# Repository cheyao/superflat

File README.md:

# Superflat - a ultra low profile bluetooth keyboard

A super flat PG1316 bluetooth split keyboard - The thickness is projected to be within 1cm. And the dimensions will be around  12x12cm

The design has it's custom USB port, battery protection & charging circuit and bluetooth nRF52840 integration.

The firmware that will be used will be zmk, and the projected battery life will be 2 months

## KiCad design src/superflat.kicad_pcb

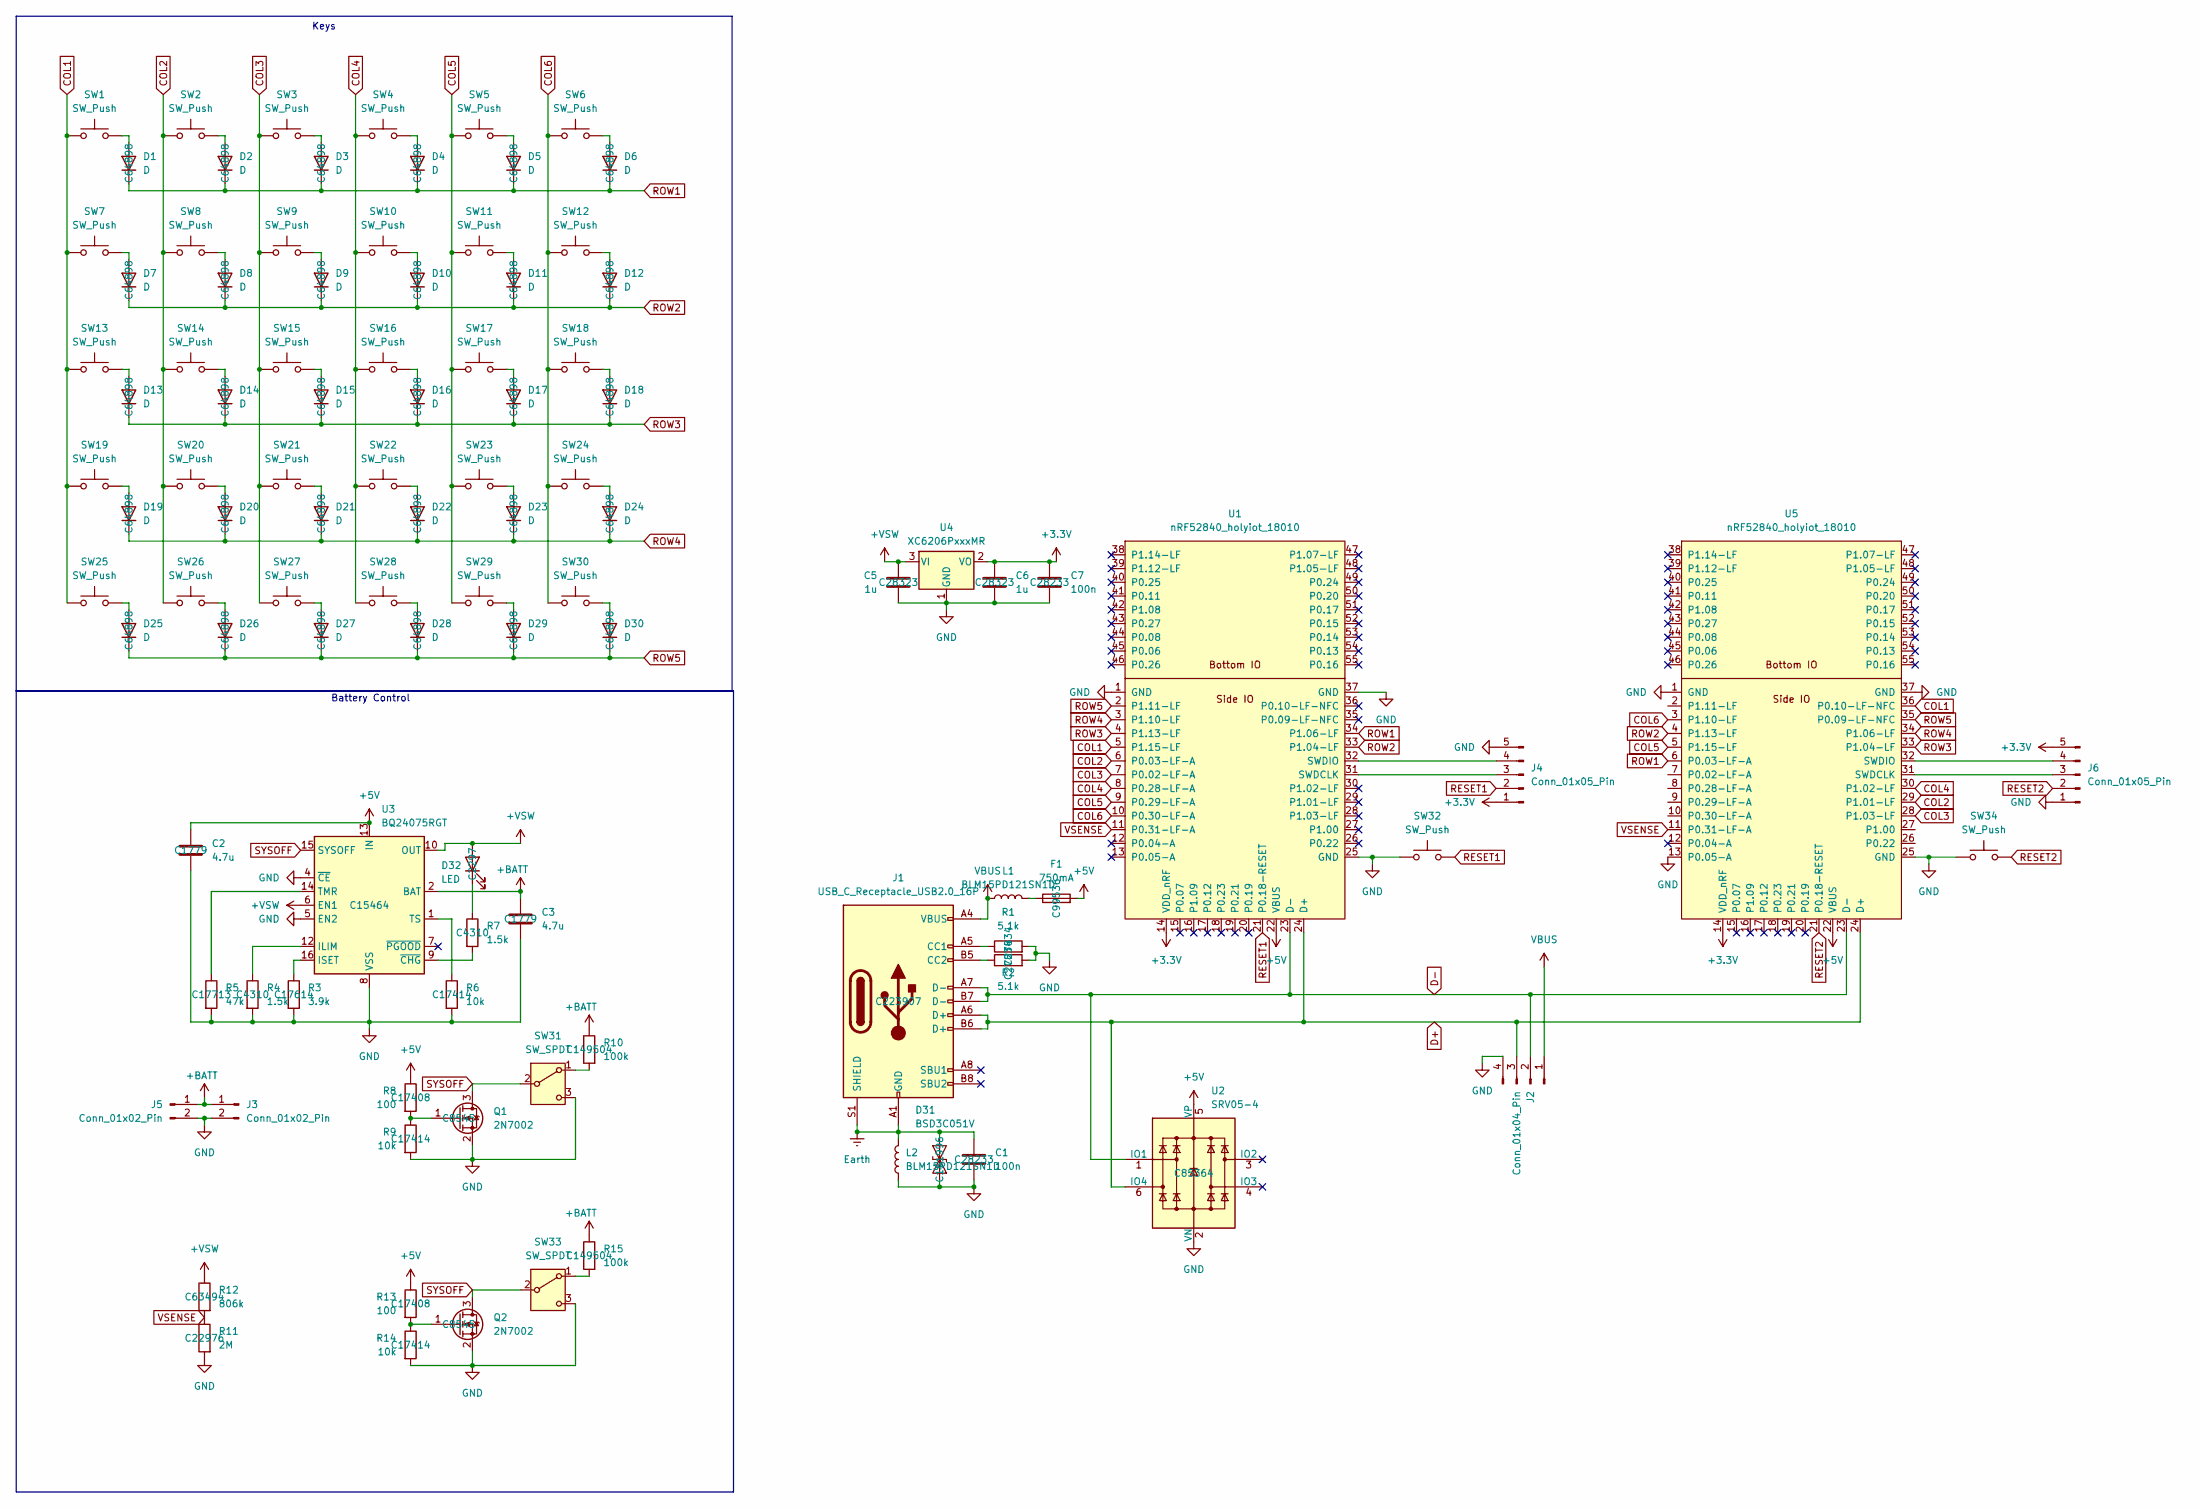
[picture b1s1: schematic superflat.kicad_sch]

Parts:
C1, C7: 100n; C_0805_2012Metric_Pad1.18x1.45mm_HandSolder; LCSC C28233
C2, C3: 4.7u; C_0805_2012Metric_Pad1.18x1.45mm_HandSolder; LCSC C1779
C5, C6: 1u; C_0805_2012Metric_Pad1.18x1.45mm_HandSolder; LCSC C28323
D1, D2, D3, D4, D5, D6, D7, D8, D9, D10, D11, D12, D13, D14, D15, D16, D17, D18, D19, D20, D21, D22, D23, D24, D25, D26, D27, D28, D29, D30: D; D_SOD-123F; LCSC C64898
D31: BSD3C051V; D_SMA; LCSC C151996
D32: LED; LED_0805_2012Metric_Pad1.15x1.40mm_HandSolder; LCSC C2297
F1: 750mA; Fuse_1206_3216Metric_Pad1.42x1.75mm_HandSolder; LCSC C99536
J1: USB_C_Receptacle_USB2.0_16P; USB_C_Receptacle_HRO_TYPE-C-31-M-14; LCSC C223907
J2: Conn_01x04_Pin; PinHeader_1x04_P2.54mm_Vertical
J3, J5: Conn_01x02_Pin; PinHeader_1x02_P2.54mm_Vertical
J4, J6: Conn_01x05_Pin; PinHeader_1x05_P2.54mm_Vertical
L1, L2: BLM15PD121SN1D; L_0402_1005Metric_Pad0.77x0.64mm_HandSolder
Q1, Q2: 2N7002; SOT-23; LCSC C8545
R1, R2: 5.1k; R_0805_2012Metric_Pad1.20x1.40mm_HandSolder; LCSC C27834
R3: 3.9k; R_0805_2012Metric_Pad1.20x1.40mm_HandSolder; LCSC C17614
R4, R7: 1.5k; R_0805_2012Metric_Pad1.20x1.40mm_HandSolder; LCSC C4310
R5: 47k; R_0805_2012Metric_Pad1.20x1.40mm_HandSolder; LCSC C17713
R6, R9, R14: 10k; R_0805_2012Metric_Pad1.20x1.40mm_HandSolder; LCSC C17414
R8, R13: 100; R_0805_2012Metric_Pad1.20x1.40mm_HandSolder; LCSC C17408
R10, R15: 100k; R_0805_2012Metric_Pad1.20x1.40mm_HandSolder; LCSC C149504
R11: 2M; R_0603_1608Metric_Pad0.98x0.95mm_HandSolder; LCSC C22976
R12: 806k; R_0805_2012Metric_Pad1.20x1.40mm_HandSolder; LCSC C63494
SW1, SW2, SW3, SW4, SW5, SW6, SW7, SW8, SW9, SW10, SW11, SW12, SW13, SW14, SW15, SW16, SW17, SW18, SW19, SW20, SW21, SW22, SW23, SW24, SW25, SW26, SW27, SW28, SW29, SW30: SW_Push; SW_PG1316S
SW31, SW33: SW_SPDT; Slide
SW32, SW34: SW_Push; SolderJumper-2_P1.3mm_Open_RoundedPad1.0x1.5mm
U1, U5: nRF52840_holyiot_18010; nRF52840_holyiot_18010_HS_simple
U2: SRV05-4; SOT-23-6-routable; LCSC C85364
U3: BQ24075RGT; VQFN-16-1EP_3x3mm_P0.5mm_EP1.6x1.6mm; LCSC C15464
U4: XC6206PxxxMR; SOT-23-3

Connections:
+3.3V: C6.1, C7.1, J4.1, J6.5, U1.14 (VDD_nRF), U4.2 (VO), U5.14 (VDD_nRF)
+5V: C2.1, F1.2, R8.1, R13.1, U1.22 (VBUS), U2.5 (VP), U3.13 (IN), U5.22 (VBUS)
+BATT: C3.1, J3.1, J5.1, R10.1, R15.1, U3.2 (BAT), U3.3 (BAT)
+VSW: C5.1, D32.2 (A), R12.1, U3.6 (EN1), U3.10 (OUT), U3.11 (OUT), U4.3 (VI)
COL1: SW1.1, SW7.1, SW13.1, SW19.1, SW25.1, U1.5 (P1.15-LF), U5.36 (P0.10-LF-NFC)
COL2: SW2.1, SW8.1, SW14.1, SW20.1, SW26.1, U1.6 (P0.03-LF-A), U5.29 (P1.01-LF)
COL3: SW3.1, SW9.1, SW15.1, SW21.1, SW27.1, U1.7 (P0.02-LF-A), U5.28 (P1.03-LF)
COL4: SW4.1, SW10.1, SW16.1, SW22.1, SW28.1, U1.8 (P0.28-LF-A), U5.30 (P1.02-LF)
COL5: SW5.1, SW11.1, SW17.1, SW23.1, SW29.1, U1.9 (P0.29-LF-A), U5.5 (P1.15-LF)
COL6: SW6.1, SW12.1, SW18.1, SW24.1, SW30.1, U1.10 (P0.30-LF-A), U5.3 (P1.10-LF)
D+: J1.A6 (D+), J1.B6 (D+), J2.3, SW4.MP, U1.24 (D+), U2.6 (IO4), U5.24 (D+)
D-: J1.A7 (D-), J1.B7 (D-), J2.2, U1.23 (D-), U2.1 (IO1), U5.23 (D-)
Earth: C1.1, D31.2 (A2), J1.A1 (GND), J1.A12 (GND), J1.B1 (GND), J1.B12 (GND), J1.S1 (SHIELD), L2.2
GND: C1.2, C2.2, C3.2, C5.2, C6.2, C7.2, D31.1 (A1), J2.4, J3.2, J4.5, J5.2, J6.1, L2.1, Q1.2 (S), Q2.2 (S), R1.2, R2.2, R3.2, R4.2, R5.2, R6.2, R9.2, R11.2, R14.2, SW5.MP, SW6.MP, SW7.MP, SW31.3 (C), SW32.1, SW33.3 (C), SW34.1, U1.1 (GND), U1.25 (GND), U1.37 (GND), U2.2 (VN), U3.4 (~CE), U3.5 (EN2), U3.8 (VSS), U3.17 (VSS), U4.1 (GND), U5.1 (GND), U5.13 (P0.05-A), U5.25 (GND), U5.37 (GND)
unnamed: D1.2 (A), SW1.2
unnamed: D2.2 (A), SW2.2
unnamed: D3.2 (A), SW3.2
unnamed: D4.2 (A), SW4.2
unnamed: D5.2 (A), SW5.2
unnamed: D6.2 (A), SW6.2
unnamed: D7.2 (A), SW7.2
unnamed: D8.2 (A), SW8.2
unnamed: D9.2 (A), SW9.2
unnamed: D10.2 (A), SW10.2
unnamed: D11.2 (A), SW11.2
unnamed: D12.2 (A), SW12.2
unnamed: D13.2 (A), SW13.2
unnamed: D14.2 (A), SW14.2
unnamed: D15.2 (A), SW15.2
unnamed: D16.2 (A), SW16.2
unnamed: D17.2 (A), SW17.2
unnamed: D18.2 (A), SW18.2
unnamed: D19.2 (A), SW19.2
unnamed: D20.2 (A), SW20.2
unnamed: D21.2 (A), SW21.2
unnamed: D22.2 (A), SW22.2
unnamed: D23.2 (A), SW23.2
unnamed: D24.2 (A), SW24.2
unnamed: D25.2 (A), SW25.2
unnamed: D26.2 (A), SW26.2
unnamed: D27.2 (A), SW27.2
unnamed: D28.2 (A), SW28.2
unnamed: D29.2 (A), SW29.2
unnamed: D30.2 (A), SW30.2
unnamed: D32.1 (K), R7.1
unnamed: F1.1, L1.2
unnamed: J1.A5 (CC1), R1.1
unnamed: J1.B5 (CC2), R2.1
unnamed: J4.3, U1.31 (SWDCLK)
unnamed: J4.4, U1.32 (SWDIO)
unnamed: J6.3, U5.31 (SWDCLK)
unnamed: J6.4, U5.32 (SWDIO)
unnamed: Q1.1 (G), R8.2, R9.1
unnamed: Q2.1 (G), R13.2, R14.1
unnamed: R10.2, SW31.1 (A)
unnamed: R15.2, SW33.1 (A)
unnamed: R4.1, U3.12 (ILIM)
unnamed: R3.1, U3.16 (ISET)
unnamed: R5.1, U3.14 (TMR)
unnamed: R6.1, U3.1 (TS)
unnamed: R7.2, U3.9 (~CHG)
RESET1: J4.2, SW32.2, U1.21 (P0.18-RESET)
RESET2: J6.2, SW34.2, U5.21 (P0.18-RESET)
ROW1: D1.1 (K), D2.1 (K), D3.1 (K), D4.1 (K), D5.1 (K), D6.1 (K), U1.34 (P1.06-LF), U5.6 (P0.03-LF-A)
ROW2: D7.1 (K), D8.1 (K), D9.1 (K), D10.1 (K), D11.1 (K), D12.1 (K), U1.33 (P1.04-LF), U5.4 (P1.13-LF)
ROW3: D13.1 (K), D14.1 (K), D15.1 (K), D16.1 (K), D17.1 (K), D18.1 (K), U1.4 (P1.13-LF), U5.33 (P1.04-LF)
ROW4: D19.1 (K), D20.1 (K), D21.1 (K), D22.1 (K), D23.1 (K), D24.1 (K), U1.3 (P1.10-LF), U5.34 (P1.06-LF)
ROW5: D25.1 (K), D26.1 (K), D27.1 (K), D28.1 (K), D29.1 (K), D30.1 (K), U1.2 (P1.11-LF), U5.35 (P0.09-LF-NFC)
SYSOFF: Q1.3 (D), Q2.3 (D), SW31.2 (B), SW33.2 (B), U3.15 (SYSOFF)
VBUS: J1.A4 (VBUS), J1.A9 (VBUS), J1.B4 (VBUS), J1.B9 (VBUS), J2.1, L1.1
VSENSE: R11.1, R12.2, U1.11 (P0.31-LF-A), U5.11 (P0.31-LF-A)

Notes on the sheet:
Battery Control
Keys

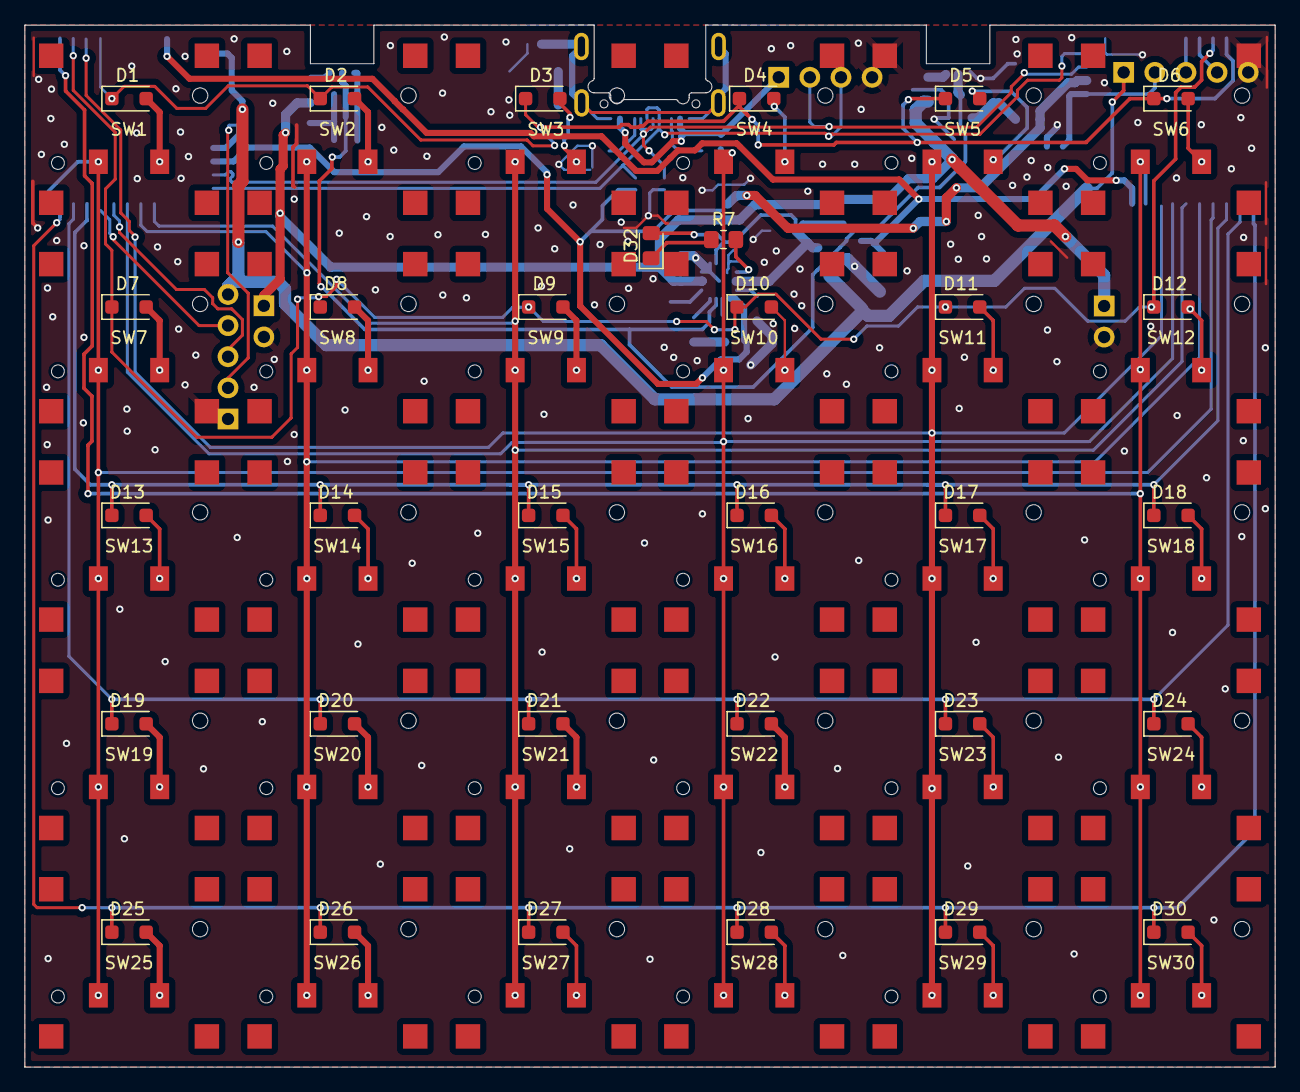
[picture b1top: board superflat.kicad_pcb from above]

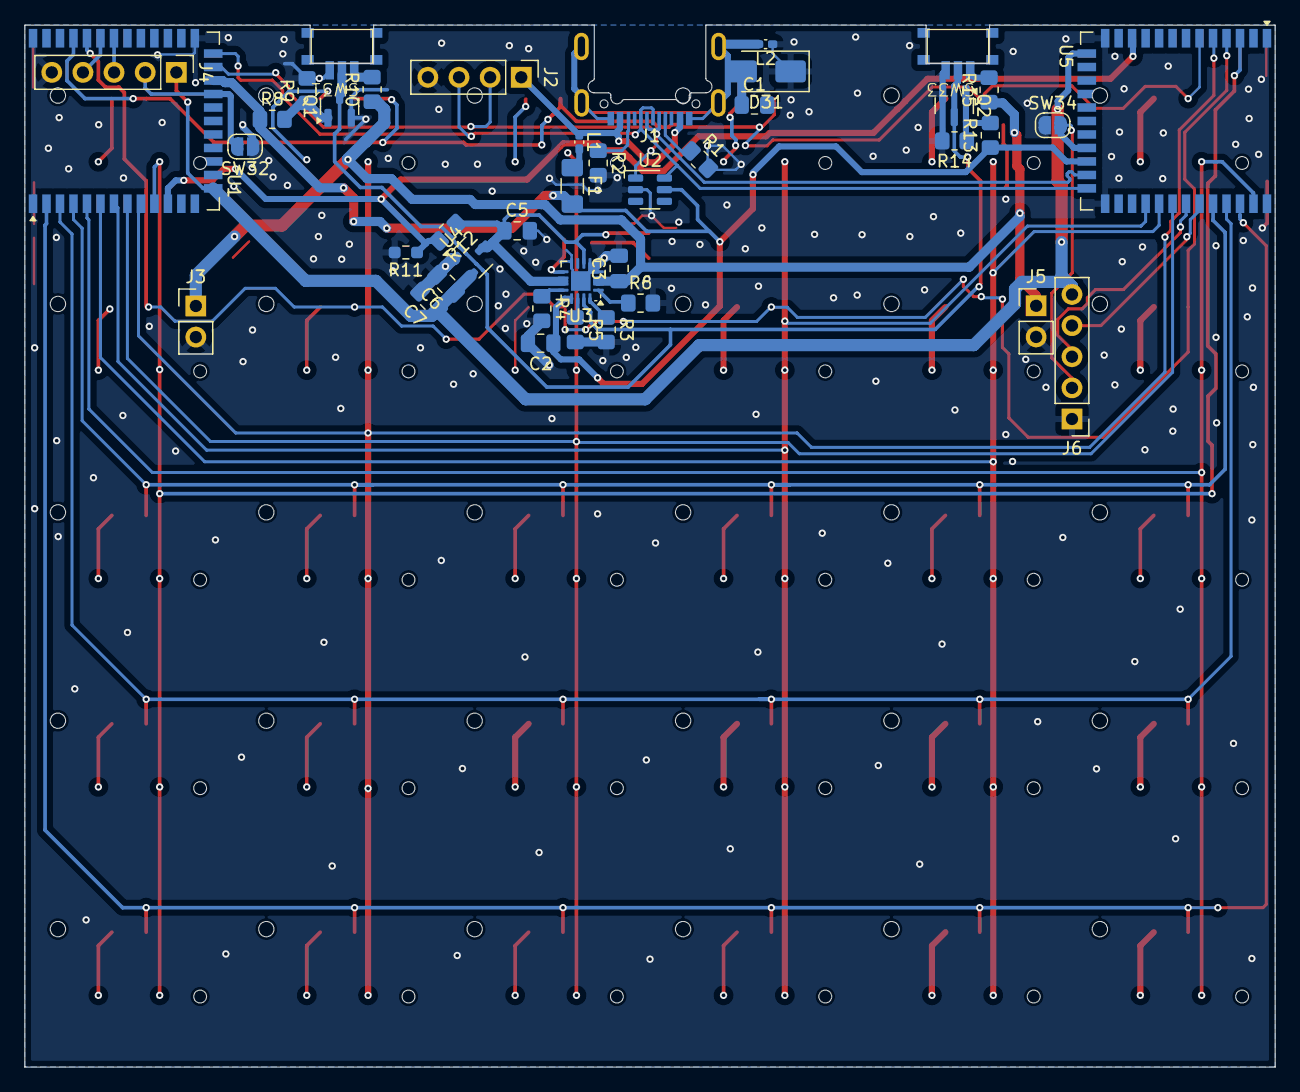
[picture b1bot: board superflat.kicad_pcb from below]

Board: 2 copper layers, 102.0 x 85.0 mm, 103 parts (41 on the bottom side), 71 nets.

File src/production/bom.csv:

Designator,Footprint,Quantity,Value,LCSC Part #
"C1, C7",0805,2,100n,C28233
"C2, C3",0805,2,4.7u,C1779
"C5, C6",0805,2,1u,C28323
"D1, D10, D11, D12, D13, D14, D15, D16, D17, D18, D19, D2, D20, D21, D22, D23, D24, D25, D26, D27, D28, D29, D3, D30, D4, D5, D6, D7, D8, D9",D_SOD-123F,30,D,C64898
D31,D_SMA,1,BSD3C051V,C151996
D32,0805,1,LED,C2297
F1,1206,1,750mA,C99536
J1,USB_C_Receptacle_HRO_TYPE-C-31-M-14,1,USB_C_Receptacle_USB2.0_16P,C223907
J2,PinHeader_1x04_P2.54mm_Vertical,1,Conn_01x04_Pin,
"J3, J5",PinHeader_1x02_P2.54mm_Vertical,2,Conn_01x02_Pin,
"J4, J6",PinHeader_1x05_P2.54mm_Vertical,2,Conn_01x05_Pin,
"L1, L2",0402,2,BLM15PD121SN1D,
"Q1, Q2",SOT-23,2,2N7002,C8545
"R1, R2",0805,2,5.1k,C27834
"R10, R15",0805,2,100k,C149504
R11,0603,1,2M,C22976
R12,0805,1,806k,C63494
"R13, R8",0805,2,100,C17408
"R14, R6, R9",0805,3,10k,C17414
R3,0805,1,3.9k,C17614
"R4, R7",0805,2,1.5k,C4310
R5,0805,1,47k,C17713
"SW1, SW10, SW11, SW12, SW13, SW14, SW15, SW16, SW17, SW18, SW19, SW2, SW20, SW21, SW22, SW23, SW24, SW25, SW26, SW27, SW28, SW29, SW3, SW30, SW4, SW5, SW6, SW7, SW8, SW9",SW_PG1316S,30,SW_Push,
"SW31, SW33",Slide,2,SW_SPDT,
"SW32, SW34",SolderJumper-2_P1.3mm_Open_RoundedPad1.0x1.5mm,2,SW_Push,
"U1, U5",nRF52840_holyiot_18010_HS_simple,2,nRF52840_holyiot_18010,
U2,SOT-23-6-routable,1,SRV05-4,C85364
U3,VQFN-16-1EP_3x3mm_P0.5mm_EP1.6x1.6mm,1,BQ24075RGT,C15464
U4,SOT-23-3,1,XC6206PxxxMR,

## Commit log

2025-04-10 Init
2025-04-13 V2 done!
2025-04-14 Final cleanup
2025-04-14 Add some pics
